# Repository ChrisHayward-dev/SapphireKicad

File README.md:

See the LastProduction branch for the most current revision

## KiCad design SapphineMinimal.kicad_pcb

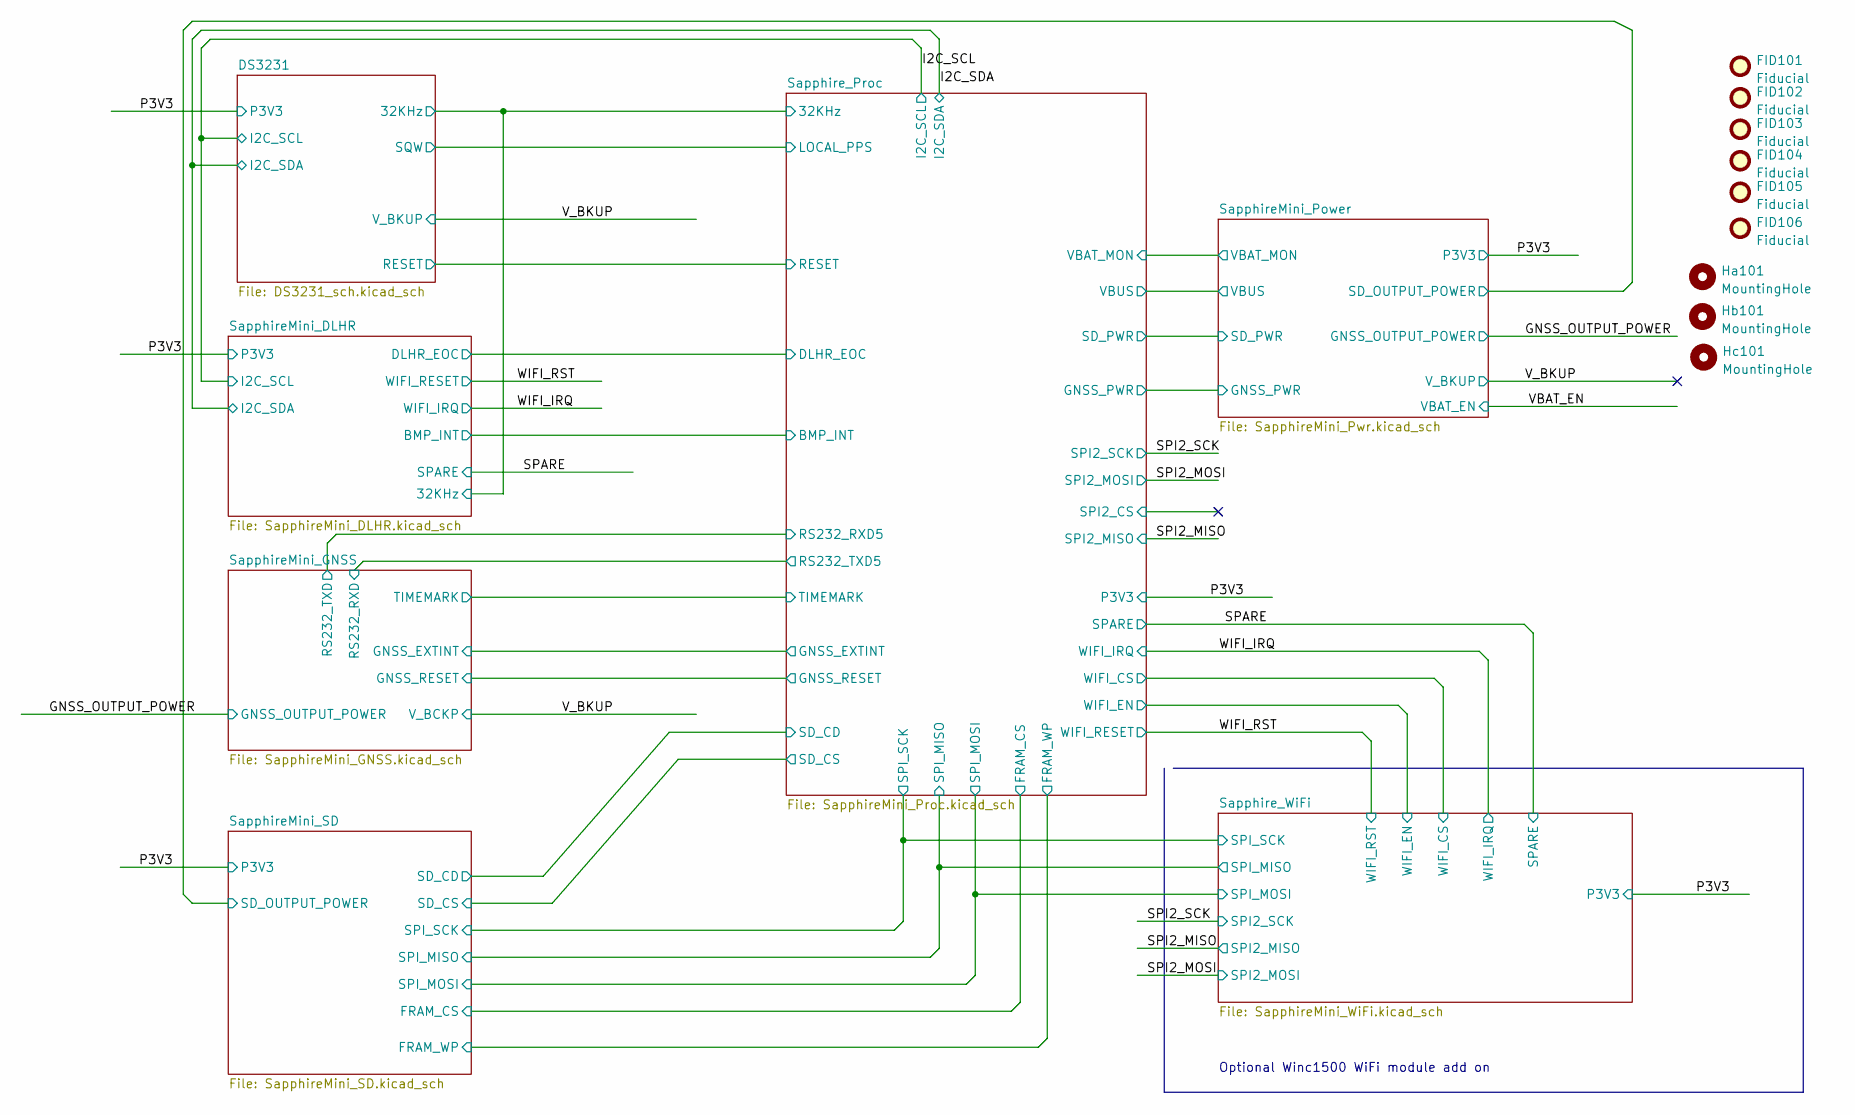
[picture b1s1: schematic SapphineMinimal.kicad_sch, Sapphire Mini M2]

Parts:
FID101, FID102, FID103, FID104, FID105, FID106: Fiducial; Fiducial_0.5mm_Mask1mm
Ha101: MountingHole; MountingHole_3.2mm_M3
Hb101: MountingHole; MountingHole_3.2mm_M3
Hc101: MountingHole; MountingHole_3.2mm_M3

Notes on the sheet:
Optional Winc1500 WiFi module add on

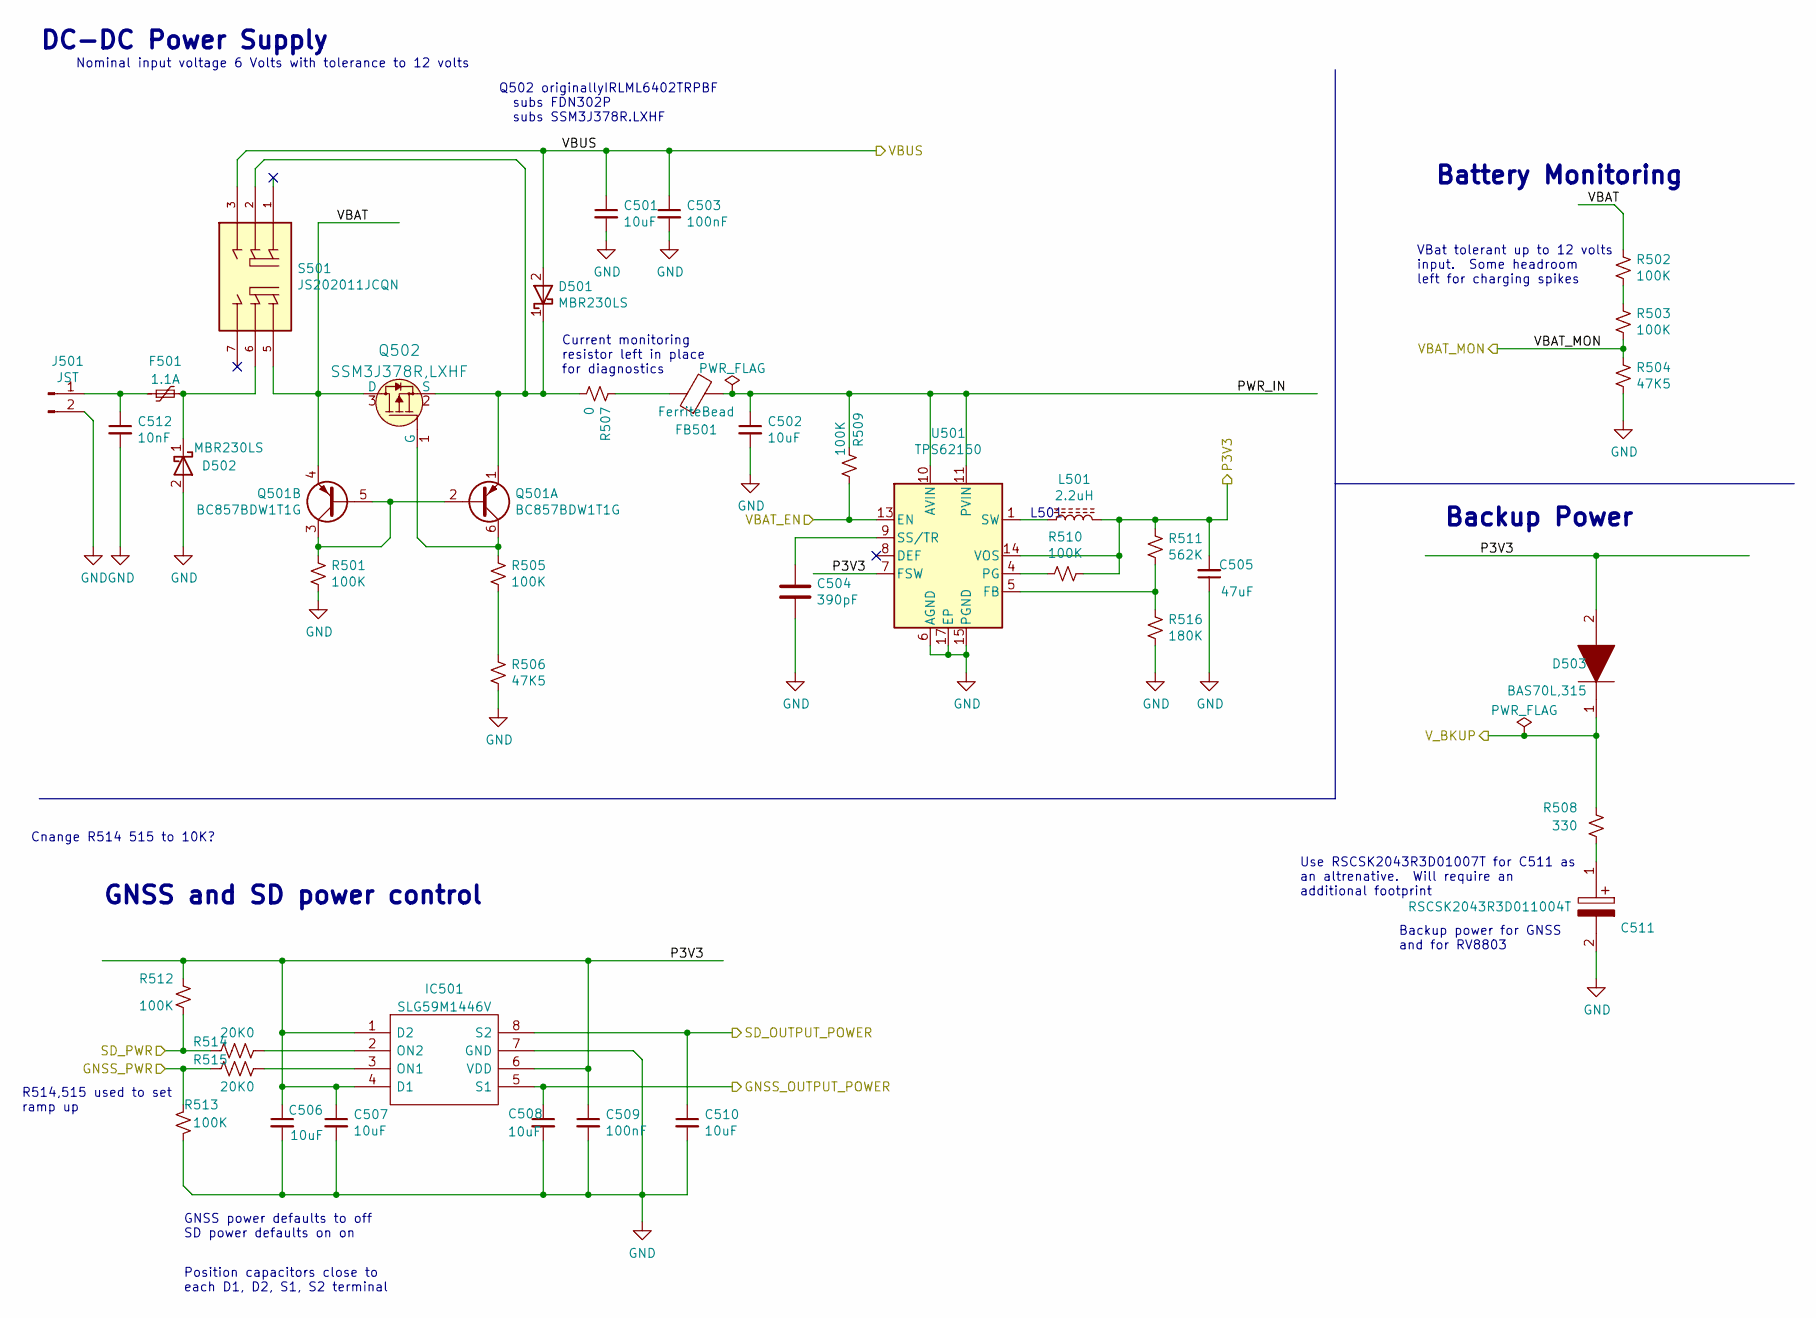
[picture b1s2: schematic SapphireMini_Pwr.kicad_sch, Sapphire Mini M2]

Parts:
C501, C506, C507, C508, C510: 10uF; C_0805_2012Metric; Voltage Rating (DC) 25 volt; Voltage 25; MPN CL21A106KAYNNNE; Digi-Key_PN 490-10748-1-ND
C502: 10uF; C_0805_2012Metric; Voltage Rating (DC) 16 volt; Voltage 16; MPN GRM21BR61E106MA73L; Digi-Key_PN 490-10748-1-ND
C503, C509: 100nF; C_0402_1005Metric; Tolerance 10%; Voltage 25; MPN CL05A104KA5NNNC; DigiKey Price 0.10
C504: 390pF; C_0603_1608Metric; MPN CL10C391JB81PNC; Digi-Key_PN 1276-2284-1-ND
C505: 47uF; C_1210_3225Metric; Voltage Rating (DC) 16 volt; Voltage 16; MPN CL32A476KOJNNNE; Digi-Key_PN 490-10748-1-ND
C511: RSCSK2043R3D011004T; RSCSK2043R3D01004T; Mouser Part Number 80-FC0H224ZFTBR24
C512: 10nF; C_0402_1005Metric; Tolerance 10%; Voltage 25; MPN CL05B103KB5NNNC; DigiKey Price 0.10
D501, D502: MBR230LS; D_SOD-123; MPN MBR230LS; DigiKey Price 0.29
D503: BAS70L,315; PESD5V0S1BL315; Mouser Part Number 771-BAS70L315
F501: 1.1A; R_1812_4532Metric; MPN 0ZCG0110CF2B
FB501: FerriteBead; L_0603_1608Metric; MPN BLM18AG221SN1D
IC501: SLG59M1446V; Manufacturer_Part_Number SLG59M1446V
J501: JST; JST_PH_S2B-PH-SM4-TB_1x02-1MP_P2.00mm_Horizontal; MPN JST S2B-PH-SM4-TB(LF)(SN); DigiKey Price 0.58
L501: 2.2uH; 74439344022; MPN 74439344022; Digi-Key_PN 732-10701-1-ND
Q501: BC857BDW1T1G; SOT-363_SC-70-6; MPN BC857BDW1T1G; DigiKey Price 0.24
Q502: SSM3J378R,LXHF; SOT-23-3; MPN SSM3J378R,LXHF; Digi-Key_PN IRLML6402PBFCT-ND
R501, R502, R503, R505, R509, R512, R513: 100K; R_0603_1608Metric; Tolerance 5%; MPN CRCW0603100KFKEAC; DigiKey Price 0.05
R504, R506: 47K5; R_0603_1608Metric; Tolerance 1%; MPN CRCW060347K5FKEAC; DigiKey Price 0.10
R507: 0; R_0603_1608Metric; MPN RMCF0603ZT0R00; Digi-Key_PN WSLJ-.1CT-ND
R508: 330; R_0603_1608Metric; Tolerance 1%; MPN RC0603JR-07330RL; DigiKey Price 0.10
R510: 100K; R_0603_1608Metric; MPN CRCW0603100KFKEAC; Digi-Key_PN 541-3950-1-ND
R511: 562K; R_0603_1608Metric; MPN CRCW0603562KFKEA; Digi-Key_PN 541-562KHCT-ND
R514, R515: 20K0; R_0603_1608Metric; MPN RMCF0603FT20K0
R516: 180K; R_0603_1608Metric; MPN CRCW0603180KFKEAC; Digi-Key_PN 541-5203-1-ND
S501: JS202011JCQN; SW_JS202011JCQN_handSolder; PARTREV 11 Nov 19; Digi-Key_PN CKN10723CT-ND
U501: TPS62150; VQFN-16-1EP_3x3mm_P0.5mm_EP1.68x1.68mm_ThermalVias; MPN TPS62150RGTT; Digi-Key_PN 296-30007-1-ND

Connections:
/GNSS_OUTPUT_POWER: C508.1, IC501.5 (S1); also elsewhere on the board
/P3V3: C505.2, C506.1, C507.1, C509.1, D503.2, IC501.1 (D2), IC501.4 (D1), IC501.6 (VDD), L501.2, R510.1, R511.1, R512.1, U501.7 (FSW), U501.14 (VOS); also elsewhere on the board
/SapphireMini_Power/GNSS_PWR: R513.1, R515.1; also elsewhere on the board
/SapphireMini_Power/PWR_IN: C502.1, FB501.2, R509.1, U501.10 (AVIN), U501.11 (PVIN), U501.12 (PVIN)
/SapphireMini_Power/SD_OUTPUT_POWER: C510.1, IC501.8 (S2); also elsewhere on the board
/SapphireMini_Power/SD_PWR: R512.2, R514.1; also elsewhere on the board
/SapphireMini_Power/VBAT: Q501.4 (E2), Q502.3 (D), R502.1, S501.5
/SapphireMini_Power/VBAT_MON: R503.2, R504.1; also elsewhere on the board
/SapphireMini_Power/VBUS: C501.1, C503.1, D501.2 (A), S501.3; also elsewhere on the board
/VBAT_EN: R509.2, U501.13 (EN)
/V_BKUP: D503.1, R508.2; also elsewhere on the board
GND: C501.2, C502.2, C503.2, C504.2, C505.1, C506.2, C507.2, C508.2, C509.2, C510.2, C511.2, C512.2, D502.2 (A), IC501.7 (GND), J501.2, R501.2, R504.2, R506.2, R513.2, R516.2, U501.6 (AGND), U501.15 (PGND), U501.16 (PGND), U501.17 (EP); also elsewhere on the board
unnamed: C504.1, U501.9 (SS/TR)
unnamed: C511.1, R508.1
unnamed: C512.1, F501.1, J501.1
unnamed: D501.1 (K), Q501.1 (E1), Q502.2 (S), R507.1, S501.2
unnamed: D502.1 (K), F501.2, S501.6
unnamed: FB501.1, R507.2
unnamed: IC501.2 (ON2), R514.2
unnamed: IC501.3 (ON1), R515.2
unnamed: L501.1, U501.1 (SW), U501.2 (SW), U501.3 (SW)
unnamed: Q501.2 (B1), Q501.3 (C2), Q501.5 (B2), R501.1
unnamed: Q501.6 (C1), Q502.1 (G), R505.1
unnamed: R502.2, R503.1
unnamed: R505.2, R506.1
unnamed: R510.2, U501.4 (PG)
unnamed: R511.2, R516.1, U501.5 (FB)

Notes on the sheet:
L501
R514,515 used to set ramp up
Current monitoring resistor left in place for diagnostics
GNSS power defaults to off SD power defaults on on
DC-DC Power Supply
VBat tolerant up to 12 volts input. Some headroom left for charging spikes
Battery Monitoring
Position capacitors close to each D1, D2, S1, S2 terminal
Nominal input voltage 6 Volts with tolerance to 12 volts
Backup Power
Use RSCSK2043R3D01007T for C511 as an altrenative. Will require an additional footprint
Cnange R514 515 to 10K?
Backup power for GNSS and for RV8803
Q502 originallyIRLML6402TRPBF subs FDN302P subs SSM3J378R.LXHF
GNSS and SD power control

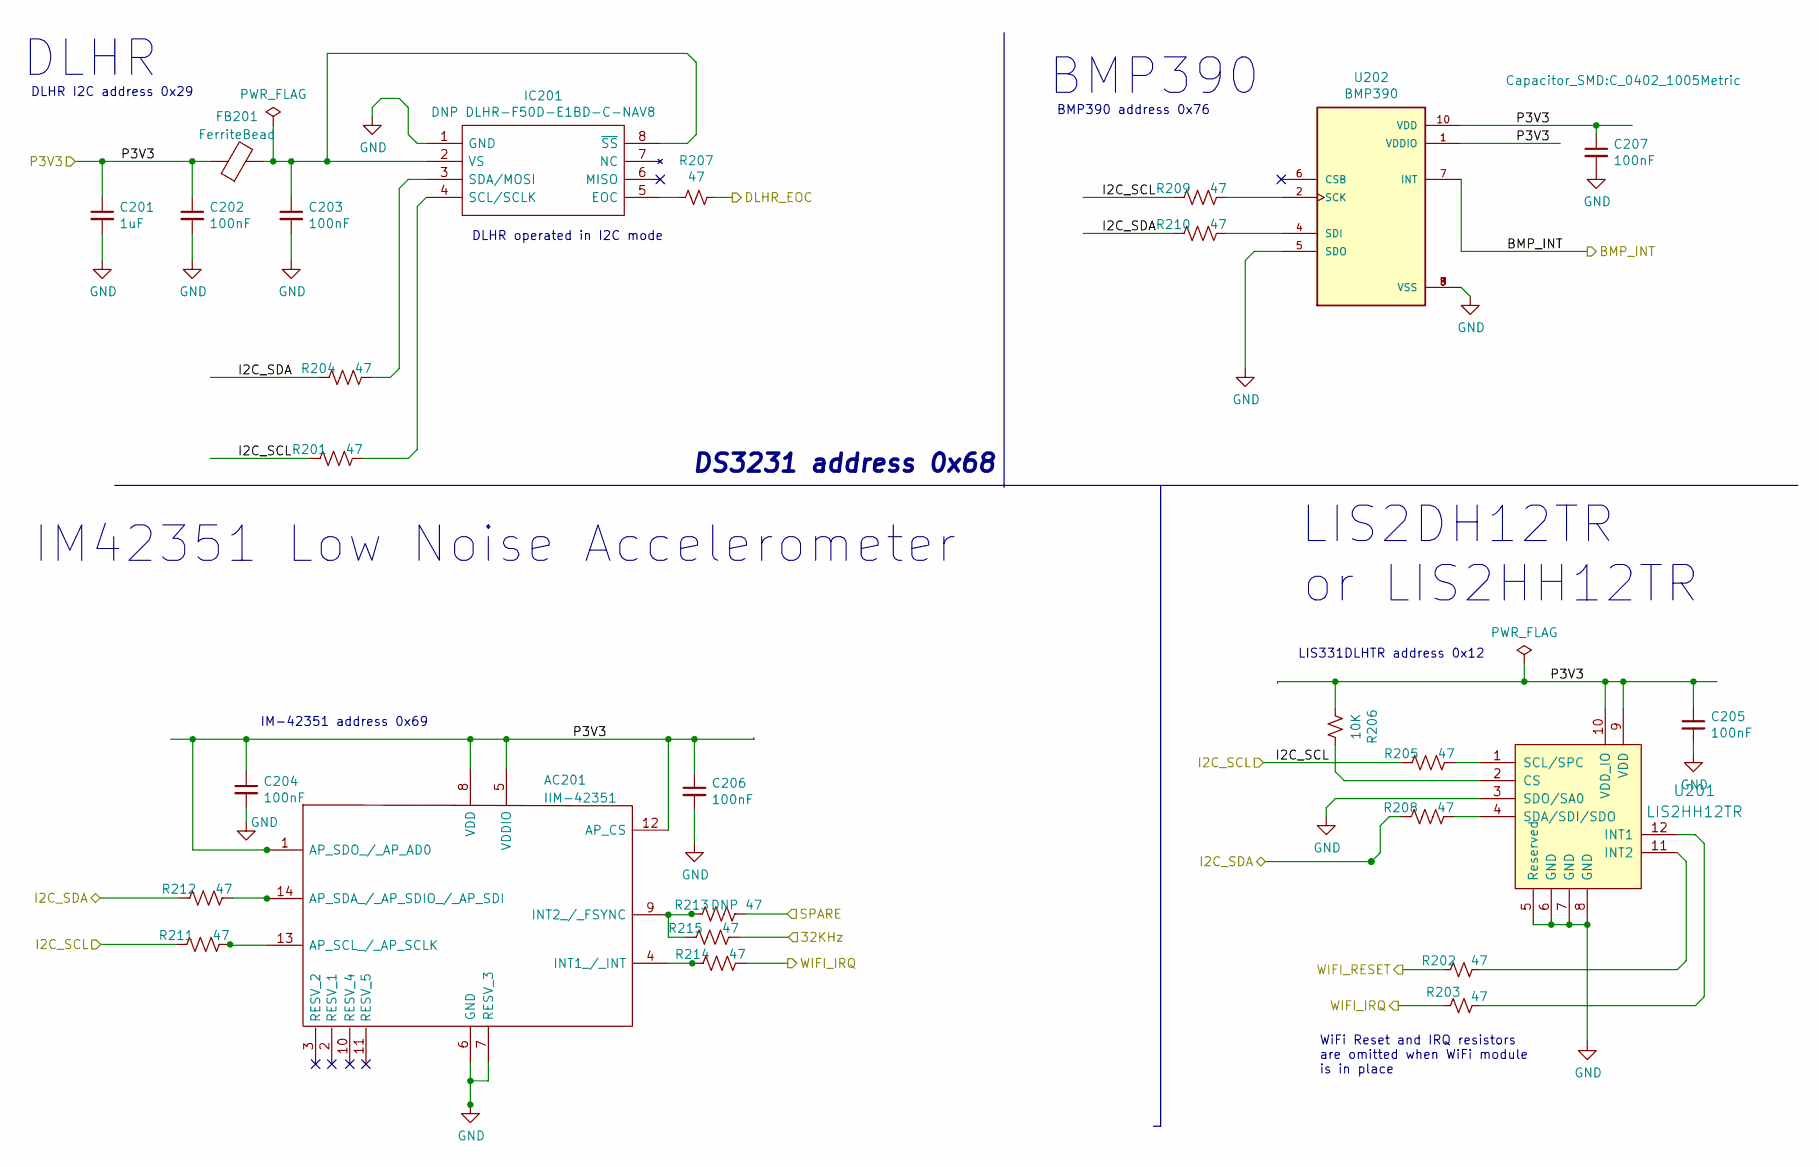
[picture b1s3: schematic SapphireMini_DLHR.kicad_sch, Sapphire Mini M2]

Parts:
AC201: IIM-42351; IIM42352; Manufacturer_Part_Number IIM-42351; Mouser Part Number 410-IIM-42351
C201: 1uF; C_0805_2012Metric; Tolerance 10%; Voltage 16; MPN CL21B105KOFNNNG; DigiKey Price 0.06
C202, C203, C204, C205, C206, C207: 100nF; C_0402_1005Metric; Tolerance 10%; Voltage 25; MPN CL05A104KA5NNNC; DigiKey Price 0.10
FB201: FerriteBead; L_0603_1608Metric; MPN BLM18AG221SN1D
IC201: DNP DLHR-F50D-E1BD-C-NAV8; DLHRF50DE1BDCNAV8; Manufacturer_Part_Number DLHR-F50D-E1BD-C-NAV8; Mouser Part Number 683-LHRF50DE1BDCNAV8
R201, R204, R205, R208, R209, R210, R211, R212, R214, R215: 47; R_0603_1608Metric; MPN CRCW060347R0FKEAC
R202, R203, R207: 47; R_0603_1608Metric; Tolerance 5%; MPN CRCW060347R0FKEAC; DigiKey Price 0.05
R206: 10K; R_0603_1608Metric; Tolerance 5%; MPN CRCW060310K0FKEAC; DigiKey Price 0.05
R213: DNP 47; R_0603_1608Metric; MPN CRCW060347R0FKEAC
U201: LIS2HH12TR; LIS2DH12TR; MPN LIS2DH12TR; Digi-Key_PN 497-14851-1-ND
U202: BMP390; BMP388; PARTREV 1.1; Digi-Key_PN 828-1079-1-ND

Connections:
/DS3231/32KHz: R215.1; also elsewhere on the board
/I2C_SCL: R201.2, R205.2, R209.2, R211.2; also elsewhere on the board
/I2C_SDA: R204.2, R208.2, R210.2, R212.2; also elsewhere on the board
/P3V3: AC201.1 (AP_SDO_/_AP_AD0), AC201.5 (VDDIO), AC201.8 (VDD), AC201.12 (AP_CS), C201.1, C202.1, C204.1, C205.1, C206.1, C207.1, FB201.1, R206.2, U201.9 (VDD), U201.10 (VDD_IO), U202.1 (VDDIO), U202.10 (VDD); also elsewhere on the board
/SPARE: R213.1; also elsewhere on the board
/SapphireMini_DLHR/BMP_INT: U202.7 (INT); also elsewhere on the board
/SapphireMini_DLHR/DLHR_EOC: R207.1; also elsewhere on the board
/WIFI_IRQ: R203.2, R214.1; also elsewhere on the board
/WIFI_RST: R202.2; also elsewhere on the board
GND: AC201.6 (GND), AC201.7 (RESV_3), C201.2, C202.2, C203.2, C204.2, C205.2, C206.2, C207.2, IC201.1 (GND), U201.3 (SDO/SA0), U201.5 (Reserved), U201.6 (GND), U201.7 (GND), U201.8 (GND), U202.3 (VSS), U202.5 (SDO), U202.8 (VSS), U202.9 (VSS); also elsewhere on the board
unnamed: AC201.4 (INT1_/_INT), R214.2
unnamed: AC201.9 (INT2_/_FSYNC), R213.2, R215.2
unnamed: AC201.13 (AP_SCL_/_AP_SCLK), R211.1
unnamed: AC201.14 (AP_SDA_/_AP_SDIO_/_AP_SDI), R212.1
unnamed: C203.1, FB201.2, IC201.2 (VS), IC201.8 (~SS)
unnamed: IC201.3 (SDA/MOSI), R204.1
unnamed: IC201.4 (SCL/SCLK), R201.1
unnamed: IC201.5 (EOC), R207.2
unnamed: R202.1, U201.11 (INT2)
unnamed: R203.1, U201.12 (INT1)
unnamed: R205.1, U201.1 (SCL/SPC)
unnamed: R206.1, U201.2 (CS)
unnamed: R208.1, U201.4 (SDA/SDI/SDO)
unnamed: R209.1, U202.2 (SCK)
unnamed: R210.1, U202.4 (SDI)

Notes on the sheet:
IM-42351 address 0x69
BMP390 address 0x76
LIS2DH12TR
LIS331DLHTR address 0x12
or LIS2HH12TR
DLHR operated in I2C mode
BMP390
DLHR
DS3231 address 0x68
IM42351 Low Noise Accelerometer
WiFi Reset and IRQ resistors are omitted when WiFi module is in place
DLHR I2C address 0x29

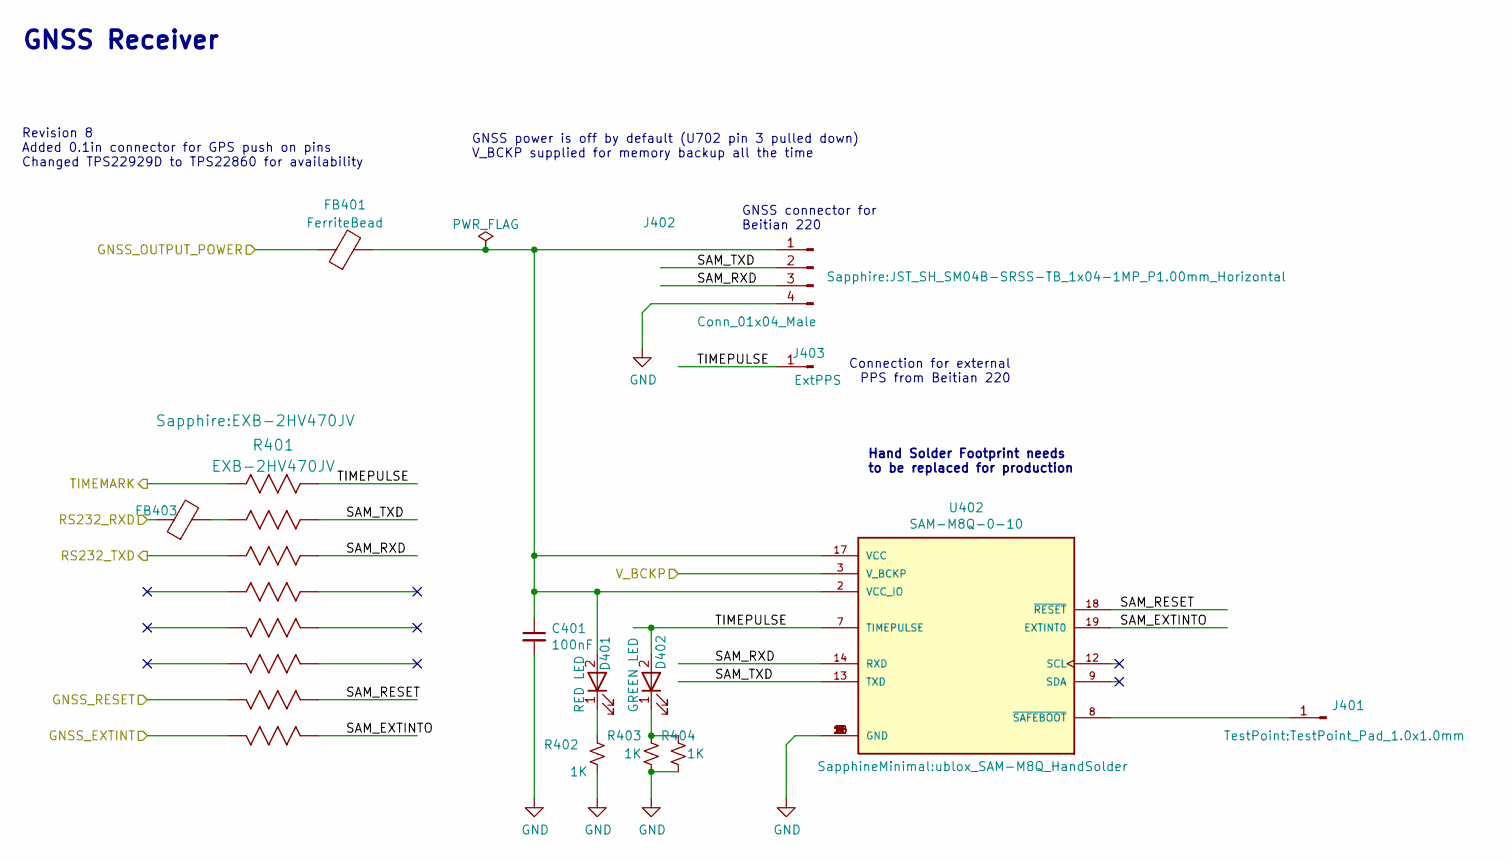
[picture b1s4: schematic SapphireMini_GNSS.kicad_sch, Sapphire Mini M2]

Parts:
C401: 100nF; C_0402_1005Metric; Tolerance 10%; Voltage 25; MPN CL05A104KA5NNNC; DigiKey Price 0.10
D401: RED LED; LED_0805_2012Metric; MPN LTST-S220KRKT; DigiKey Price 0.28
D402: GREEN LED; LED_0805_2012Metric; MPN LTST-S220KGKT; DigiKey Price 0.28
FB401, FB403: FerriteBead; L_0603_1608Metric; MPN BLM18AG221SN1D
J401: DNP Conn_01x01_Male; TestPoint_Pad_1.0x1.0mm; MPN DNP
J402: Conn_01x04_Male; JST_SH_SM04B-SRSS-TB_1x04-1MP_P1.00mm_Horizontal; MPN SM04B-SRSS-TB(LF)(SN); Digi-Key_PN 455-1804-1-ND
J403: ExtPPS; TestPoint_Pad_1.5x1.5mm
R401: EXB-2HV470JV; MPN EXB-2HV470JV
R402, R403, R404: 1K; R_0603_1608Metric; Tolerance 5%; MPN CRCW06031K00FKEAC; DigiKey Price 0.05
U402: SAM-M8Q-0-10; ublox_SAM-M8Q_HandSolder; PARTREV R07

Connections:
/GNSS_OUTPUT_POWER: FB401.1; also elsewhere on the board
/SapphireMini_GNSS/GNSS_EXTINT: R401.8; also elsewhere on the board
/SapphireMini_GNSS/GNSS_RESET: R401.7; also elsewhere on the board
/SapphireMini_GNSS/RS232_RXD: FB403.1; also elsewhere on the board
/SapphireMini_GNSS/RS232_TXD: R401.3; also elsewhere on the board
/SapphireMini_GNSS/SAM_EXTINTO: R401.9, U402.19 (EXTINT0)
/SapphireMini_GNSS/SAM_RESET: R401.10, U402.18 (~RESET)
/SapphireMini_GNSS/SAM_RXD: J402.3, R401.14, U402.14 (RXD)
/SapphireMini_GNSS/SAM_TXD: J402.2, R401.15, U402.13 (TXD)
/SapphireMini_GNSS/TIMEPULSE: D402.2 (A), J403.1, R401.16, U402.7 (TIMEPULSE)
/Sapphire_Proc/TIMEMARK: R401.1; also elsewhere on the board
/V_BKUP: U402.3 (V_BCKP); also elsewhere on the board
GND: C401.2, J402.4, R402.1, R403.1, R404.1, U402.1 (GND), U402.4 (GND), U402.5 (GND), U402.6 (GND), U402.10 (GND), U402.11 (GND), U402.15 (GND), U402.16 (GND), U402.20 (GND); also elsewhere on the board
unnamed: C401.1, D401.2 (A), FB401.2, J402.1, U402.2 (VCC_IO), U402.17 (VCC)
unnamed: D401.1 (K), R402.2
unnamed: D402.1 (K), R403.2, R404.2
unnamed: FB403.2, R401.2
unnamed: J401.1, U402.8 (~SAFEBOOT)

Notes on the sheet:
Revision 8 Added 0.1in connector for GPS push on pins Changed TPS22929D to TPS22860 for availability
GNSS power is off by default (U702 pin 3 pulled down) V_BCKP supplied for memory backup all the time
Connection for external PPS from Beitian 220
GNSS connector for Beitian 220
GNSS Receiver
Hand Solder Footprint needs to be replaced for production

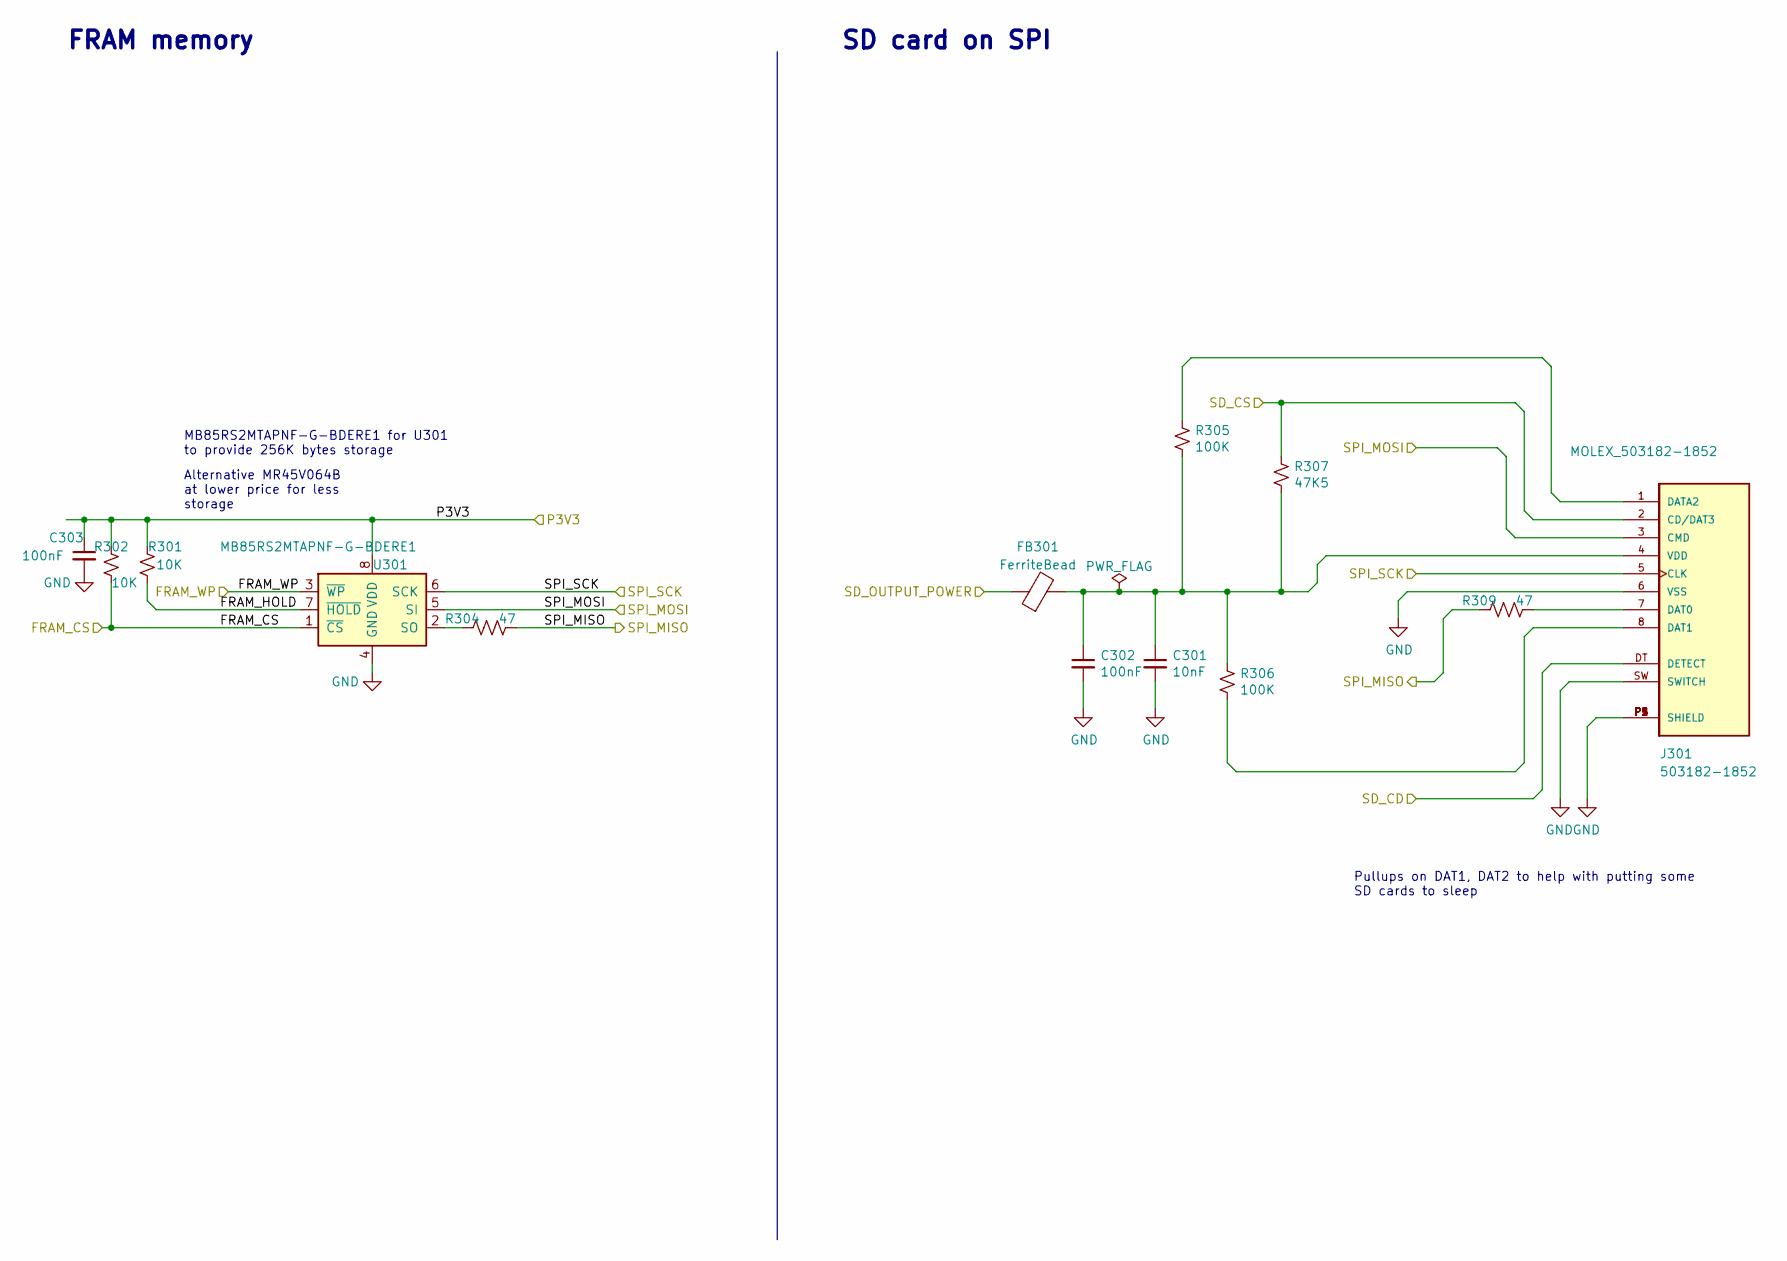
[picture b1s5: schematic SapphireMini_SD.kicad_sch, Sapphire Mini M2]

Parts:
C301: 10nF; C_0402_1005Metric; Tolerance 10%; Voltage 25; MPN CL05B103KB5NNNC; DigiKey Price 0.10
C302, C303: 100nF; C_0402_1005Metric; Tolerance 10%; Voltage 25; MPN CL05A104KA5NNNC; DigiKey Price 0.10
FB301: FerriteBead; L_0603_1608Metric; MPN BLM18AG221SN1D
J301: 503182-1852; MOLEX_503182-1852; MPN 503182-1852
R301, R302: 10K; R_0603_1608Metric; Tolerance 5%; MPN CRCW060310K0FKEAC; DigiKey Price 0.05
R304, R309: 47; R_0603_1608Metric; MPN CRCW060347R0FKEAC
R305, R306: 100K; R_0603_1608Metric; Tolerance 5%; MPN CRCW0603100KFKEAC; DigiKey Price 0.05
R307: 47K5; R_0603_1608Metric; Tolerance 1%; MPN CRCW060347K5FKEAC; DigiKey Price 0.10
U301: MB85RS2MTAPNF-G-BDERE1; SOP-8_3.9x4.9mm_P1.27mm; MPN MB85RS2MTAPNF-G-BDERE1; Digi-Key_PN MR45V064BMAZAATLCT-ND

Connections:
/P3V3: C303.1, R301.2, R302.2, U301.8 (VDD); also elsewhere on the board
/SapphireMini_Power/SD_OUTPUT_POWER: FB301.1; also elsewhere on the board
/SapphireMini_SD/FRAM_CS: R302.1, U301.1 (~CS); also elsewhere on the board
/SapphireMini_SD/FRAM_HOLD: R301.1, U301.7 (~HOLD)
/SapphireMini_SD/FRAM_WP: U301.3 (~WP); also elsewhere on the board
/SapphireMini_SD/SD_CS: J301.2 (CD/DAT3), R307.2; also elsewhere on the board
/SapphireMini_SD/SPI_MISO: R304.1, R309.2; also elsewhere on the board
/SapphireMini_SD/SPI_MOSI: J301.3 (CMD), U301.5 (SI); also elsewhere on the board
/SapphireMini_SD/SPI_SCK: J301.5 (CLK), U301.6 (SCK); also elsewhere on the board
/Sapphire_Proc/SD_CD: J301.DT (DETECT); also elsewhere on the board
GND: C301.2, C302.2, C303.2, J301.6 (VSS), J301.P1 (SHIELD), J301.P2 (SHIELD), J301.P3 (SHIELD), J301.P4 (SHIELD), J301.P5 (SHIELD), J301.SW (SWITCH), U301.4 (GND); also elsewhere on the board
unnamed: C301.1, C302.1, FB301.2, J301.4 (VDD), R305.2, R306.1, R307.1
unnamed: J301.1 (DATA2), R305.1
unnamed: J301.7 (DAT0), R309.1
unnamed: J301.8 (DAT1), R306.2
unnamed: R304.2, U301.2 (SO)

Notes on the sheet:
FRAM memory
Alternative MR45V064B at lower price for less storage
SD card on SPI
MB85RS2MTAPNF-G-BDERE1 for U301 to provide 256K bytes storage
Pullups on DAT1, DAT2 to help with putting some SD cards to sleep

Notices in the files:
parts and their libraries:
Copyright 2021 Accelerated Designs. All rights reserved.
Copyright 2016 Accelerated Designs. All rights reserved.
